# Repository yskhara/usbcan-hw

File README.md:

# usbcan-hw
PCB design files of usbcan project

utilizes ST's STM32F302CBT6 MCU.

You can get access to the firmware at https://github.com/yskhara/usbcan .
This project is currently planned to be phased out.

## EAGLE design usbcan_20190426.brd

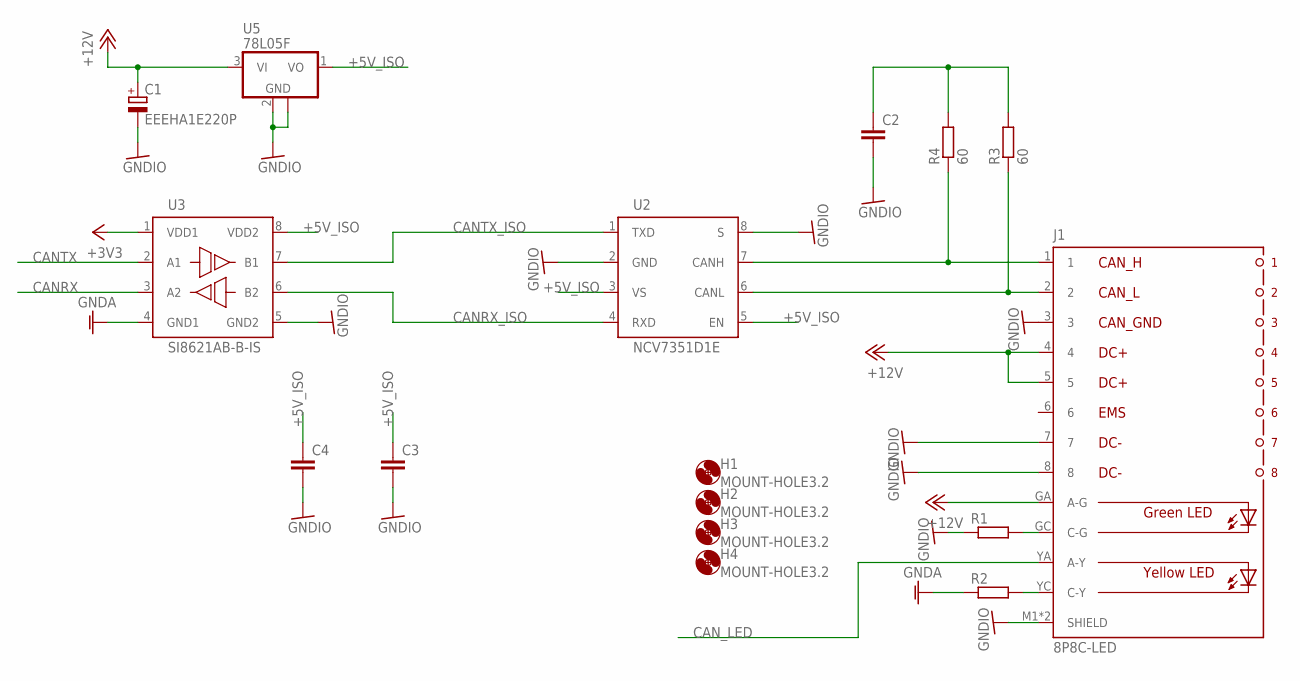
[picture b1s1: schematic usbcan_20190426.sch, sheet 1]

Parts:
C1: EEEHA1E220P; 153CLV-0605
C2, C3, C4: C-EUC0603; C0603
H1, H2, H3, H4: MOUNT-HOLE3.2; 3,2
J1: 8P8C-LED
R1, R2: R-EU_R0603; R0603
R3, R4: 60; R0603
U2: NCV7351D1E; SO08
U3: SI8621AB-B-IS; SO08
U5: 78L05F; SOT89

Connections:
+3V3: U3.1 (VDD1); also elsewhere on the board
+5V_ISO: C3.1, C4.1, U2.3 (VS), U2.5 (EN), U3.8 (VDD2), U5.1 (VO)
+12V: C1.+, J1.4, J1.5, J1.GA (A-G), U5.3 (VI)
CANH: J1.1, R4.1, U2.7 (CANH)
CANL: J1.2, R3.1, U2.6 (CANL)
CANRX: U3.3 (A2); also elsewhere on the board
CANRX_ISO: U2.4 (RXD), U3.6 (B2)
CANTX: U3.2 (A1); also elsewhere on the board
CANTX_ISO: U2.1 (TXD), U3.7 (B1)
CAN_LED: J1.YA (A-Y); also elsewhere on the board
GNDA: R2.1, U3.4 (GND1); also elsewhere on the board
GNDIO: C1.-, C2.2, C3.2, C4.2, J1.3, J1.7, J1.8, J1.M1 (SHIELD), J1.M2 (SHIELD), R1.1, U2.2 (GND), U2.8 (S), U3.5 (GND2), U5.2 (GND), U5.2@1 (GND)
unnamed: J1.GC (C-G), R1.2
unnamed: J1.YC (C-Y), R2.2
unnamed: C2.1, R3.2, R4.2

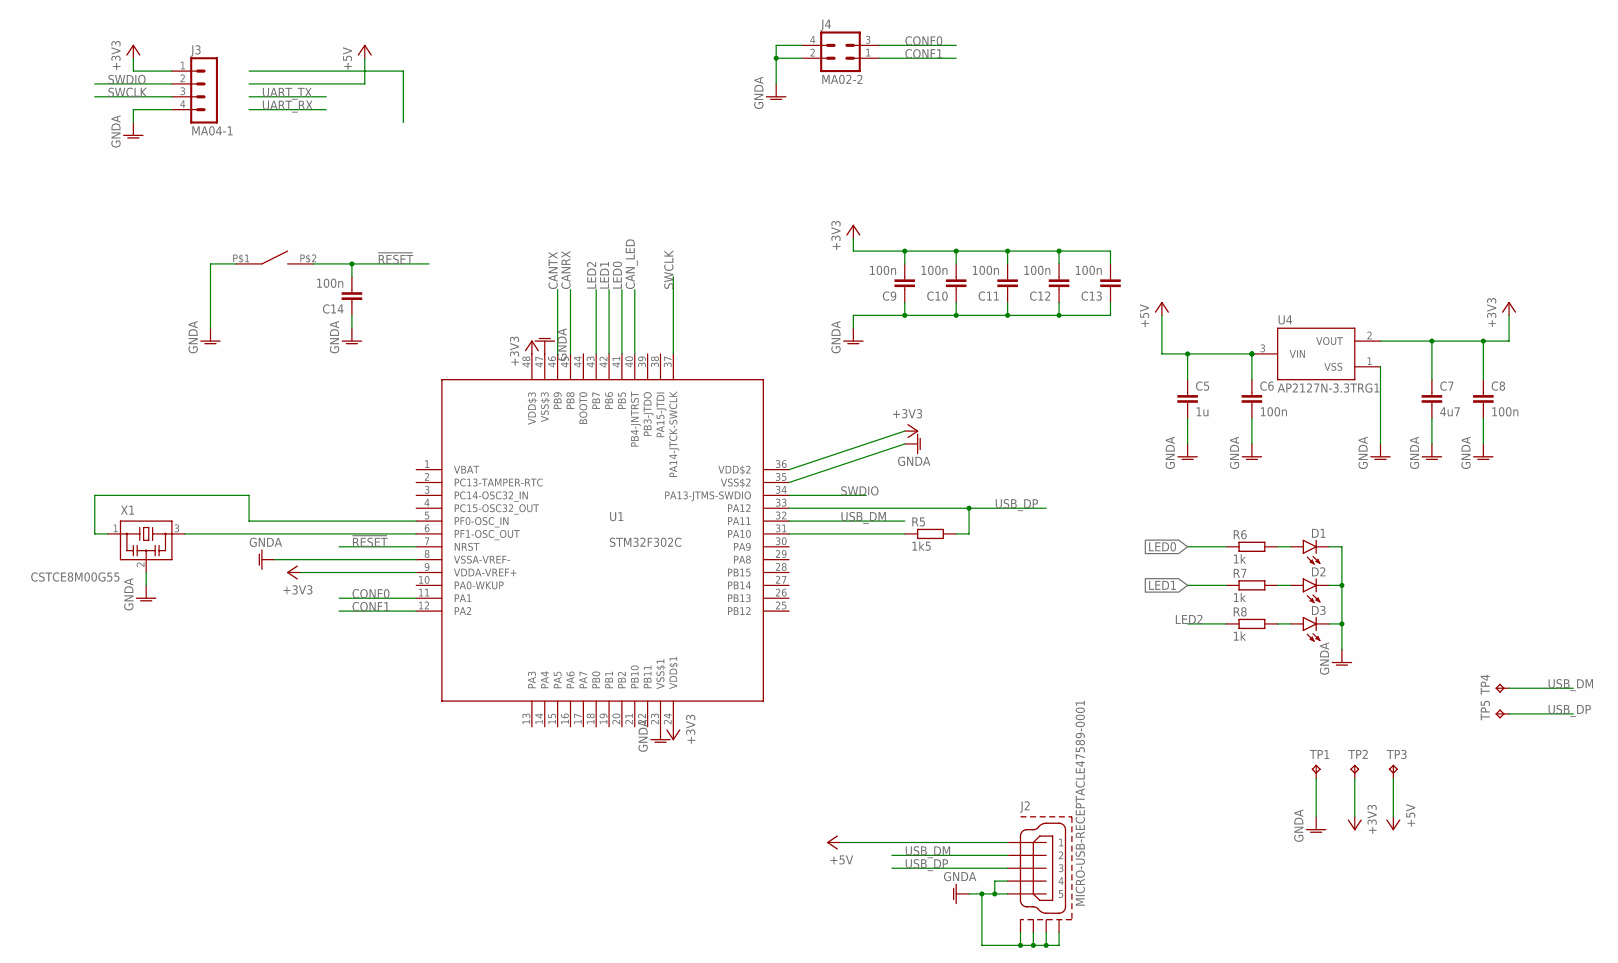
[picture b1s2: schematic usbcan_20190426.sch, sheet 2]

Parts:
C5: 1u; C0603
C6, C8, C9, C10, C11, C12, C13, C14: 100n; C0603
C7: 4u7; C0805
D1, D2, D3: LEDCHIPLED_0805; CHIPLED_0805
J2: MICRO-USB-RECEPTACLE47589-0001; 47589-0001
J3: MA04-1
J4: MA02-2; MA02-2W
R5: 1k5; R0603
R6, R7, R8: 1k; R0603
S1: SWITCH_TACTILETOP; SWITCH_TACTILE_3X6
TP1, TP2, TP3, TP4, TP5: TPB1,27; B1,27
U1: STM32F302C; LQFP48
U4: AP2127N-3.3TRG1; SOT95P240X110-3
X1: CSTCE8M00G55

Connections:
!RESET: C14.2, S1.P$2 (2), U1.7 (NRST)
+3V3: C7.1, C8.1, C9.2, C10.2, C11.2, C12.2, C13.2, J3.1, TP2.TP, U1.9 (VDDA-VREF+), U1.24 (VDD$1), U1.36 (VDD$2), U1.48 (VDD$3), U4.2 (VOUT); also elsewhere on the board
+5V: C5.1, C6.1, J2.1, TP3.TP, U4.3 (VIN)
CANRX: U1.45 (PB8); also elsewhere on the board
CANTX: U1.46 (PB9); also elsewhere on the board
CAN_LED: U1.40 (PB4-JNTRST); also elsewhere on the board
CONF0: J4.3, U1.11 (PA1)
CONF1: J4.1, U1.12 (PA2)
GNDA: C5.2, C6.2, C7.2, C8.2, C9.1, C10.1, C11.1, C12.1, C13.1, C14.1, D1.C, D2.C, D3.C, J2.4, J2.5, J2.CASING1 (GND1), J2.CASING2 (GND2), J2.CASING3 (GND3), J2.CASING4 (GND4), J2.P$1 (GND1), J2.P$2 (GND1), J2.P$3 (GND2), J2.P$4 (GND2), J3.4, J4.2, J4.4, S1.P$1 (1), TP1.TP, U1.8 (VSSA-VREF-), U1.23 (VSS$1), U1.35 (VSS$2), U1.47 (VSS$3), U4.1 (VSS), X1.2; also elsewhere on the board
LED0: R6.1, U1.41 (PB5)
LED1: R7.1, U1.42 (PB6)
LED2: R8.1, U1.43 (PB7)
unnamed: D2.A, R7.2
unnamed: D1.A, R6.2
unnamed: U1.6 (PF1-OSC_OUT), X1.3
unnamed: U1.5 (PF0-OSC_IN), X1.1
unnamed: R5.1, U1.31 (PA10)
unnamed: D3.A, R8.2
SWCLK: J3.3, U1.37 (PA14-JTCK-SWCLK)
SWDIO: J3.2, U1.34 (PA13-JTMS-SWDIO)
USB_DM: J2.2, TP4.TP, U1.32 (PA11)
USB_DP: J2.3, R5.2, TP5.TP, U1.33 (PA12)

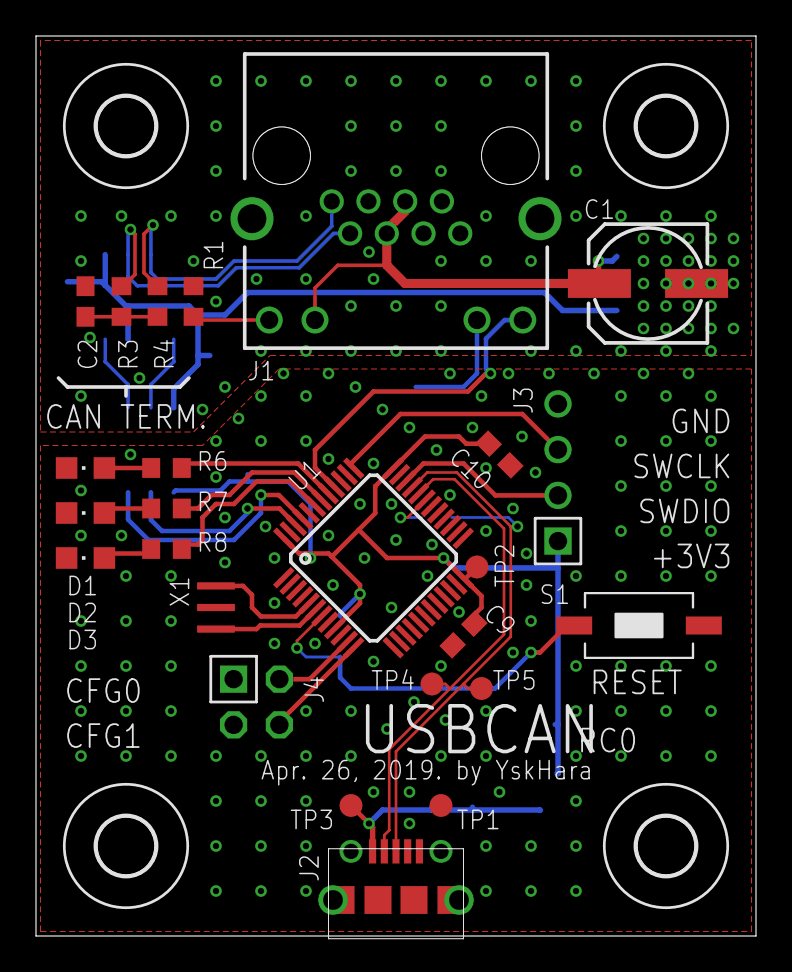
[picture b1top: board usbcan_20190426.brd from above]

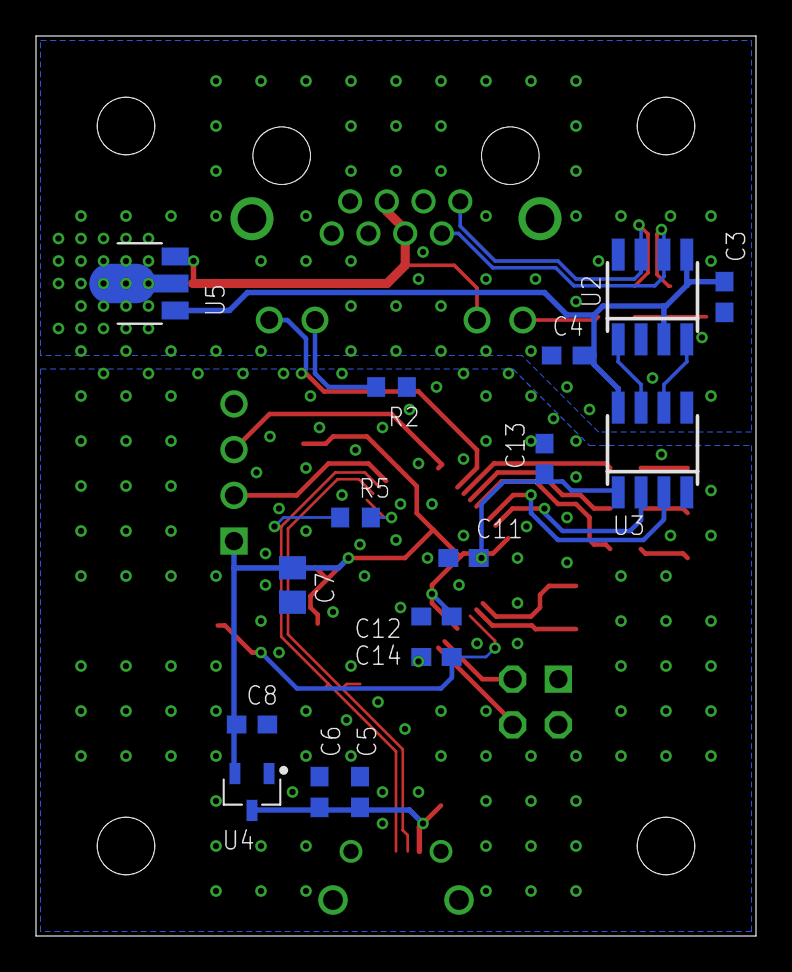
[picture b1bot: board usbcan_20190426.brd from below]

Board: 2 copper layers, 40.0 x 50.0 mm, 45 parts (16 on the bottom side), 32 nets.

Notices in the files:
parts and their libraries:
con-molex-usb: (C) 2014 Tomasz Boleslaw CEDRO, cederom@tlen.pl, http://www.tomek.cedro.info.
